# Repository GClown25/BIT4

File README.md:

# BIT4
BIT4 is a 4Bit microcontroller - fully programmable with only three buttons.

# Programming guide:

The BIT4 microcontroller has 256 Bytes of programm memory, split in 16 pages with each 16 instructions.
A instruction is 8bit wide and consists of an command and data:
\

\
To enter the programming mode, hold BTN2 down, press the RESET button once and then release BTN2.
In programming mode, step through the instructions with BTN2. When going to a new instruction, 
the leds will show the current address for a fraktion of a second.
With BTN1 the value of the command and data of the current instruction can be changed.
When stepping to a new address with BTN2, the instuction of the address above gets saved in the EEPROM.
At the end, press RESET to leave the programming mode and to start the programm execution.

## Instruction set explained:

- command 0x0: load a constant value to doutB
- command 0x1: load a constant value to doutA
- command 0x2: delay
- command 0x3: do a relative jump back
- command 0x4: load constant value to variable A
- command 0x5: load something with the value of variable A
- command 0x6: load the value of something into the variable A
- command 0x7: do arithmetic and logic operations with variable A (and B)
- command 0x8: set the high nibble of the address to jump to in absolute jump instructions
- command 0x9: do an absolute jump to the specified address
- command 0xA, 0xB: acts like a for loop. Every time this command is executed,
  if the variable C (or D) is greater than zero, an absolute jump to the specified address is done.
  Then the variable C (or D) gets decremented. 
- command 0xC: skip the next instruction if the argument is true
- command 0xD: call a function at the specified address
- command 0xE: return from the function call
- command 0xF: sets the address of the virtual 4bit RAM. 
  The value stored in this address can be read with 0x6e and written with 0x50.

## Examples:

**Blinki:**

| address | instruction |                    comment |
| :------ | :---------- | -------------------------: |
| 0       | 1f          |  turn all leds on doutA on |
| 1       | 28          |             wait for 500ms |
| 2       | 10          | turn all leds on doutB off |
| 3       | 28          |             wait for 500ms |
| 4       | 34          |           relative jump -4 |

\
**Binary counter:**
\
https://www.youtube.com/watch?v=6CpZszKlP7Y

| address | instruction |          comment |
| :------ | :---------- | ---------------: |
| 0       | 5B          |        DoutB = A |
| 1       | 59          |         PWM1 = A |
| 2       | 71          |              A++ |
| 3       | 28          |   wait for 500ms |
| 4       | 34          | relative jump -4 |

\
**Blinki with adjustable speed:**
\
https://www.youtube.com/watch?v=YPoedGGZs4g

| address   | instruction |               comment |
| :-------- | :---------- | --------------------: |
| **main:** |
| 0         | 10          |           DoutA = 0x0 |
| 1         | d5          |           call myWait |
| 2         | 1f          |           DoutA = 0xf |
| 3         | d5          |           call myWait |
| 4         | 34          |      relative jump -4 |
| **myWait:** |
| 5         | 64          |               A = Din |
| 6         | 52          |                 C = A |
| 7         | 25          |         wait for 50ms |
| 8         | a7          | for(C > 0; C--) jmp 7 |
| 9         | e0          |                return |

\
**Credits:**\
The idea for this project came from the german microcontroller learning plattform "TPS" (http://elektronik-labor.de/Lernpakete/TPS/TPS0.html).

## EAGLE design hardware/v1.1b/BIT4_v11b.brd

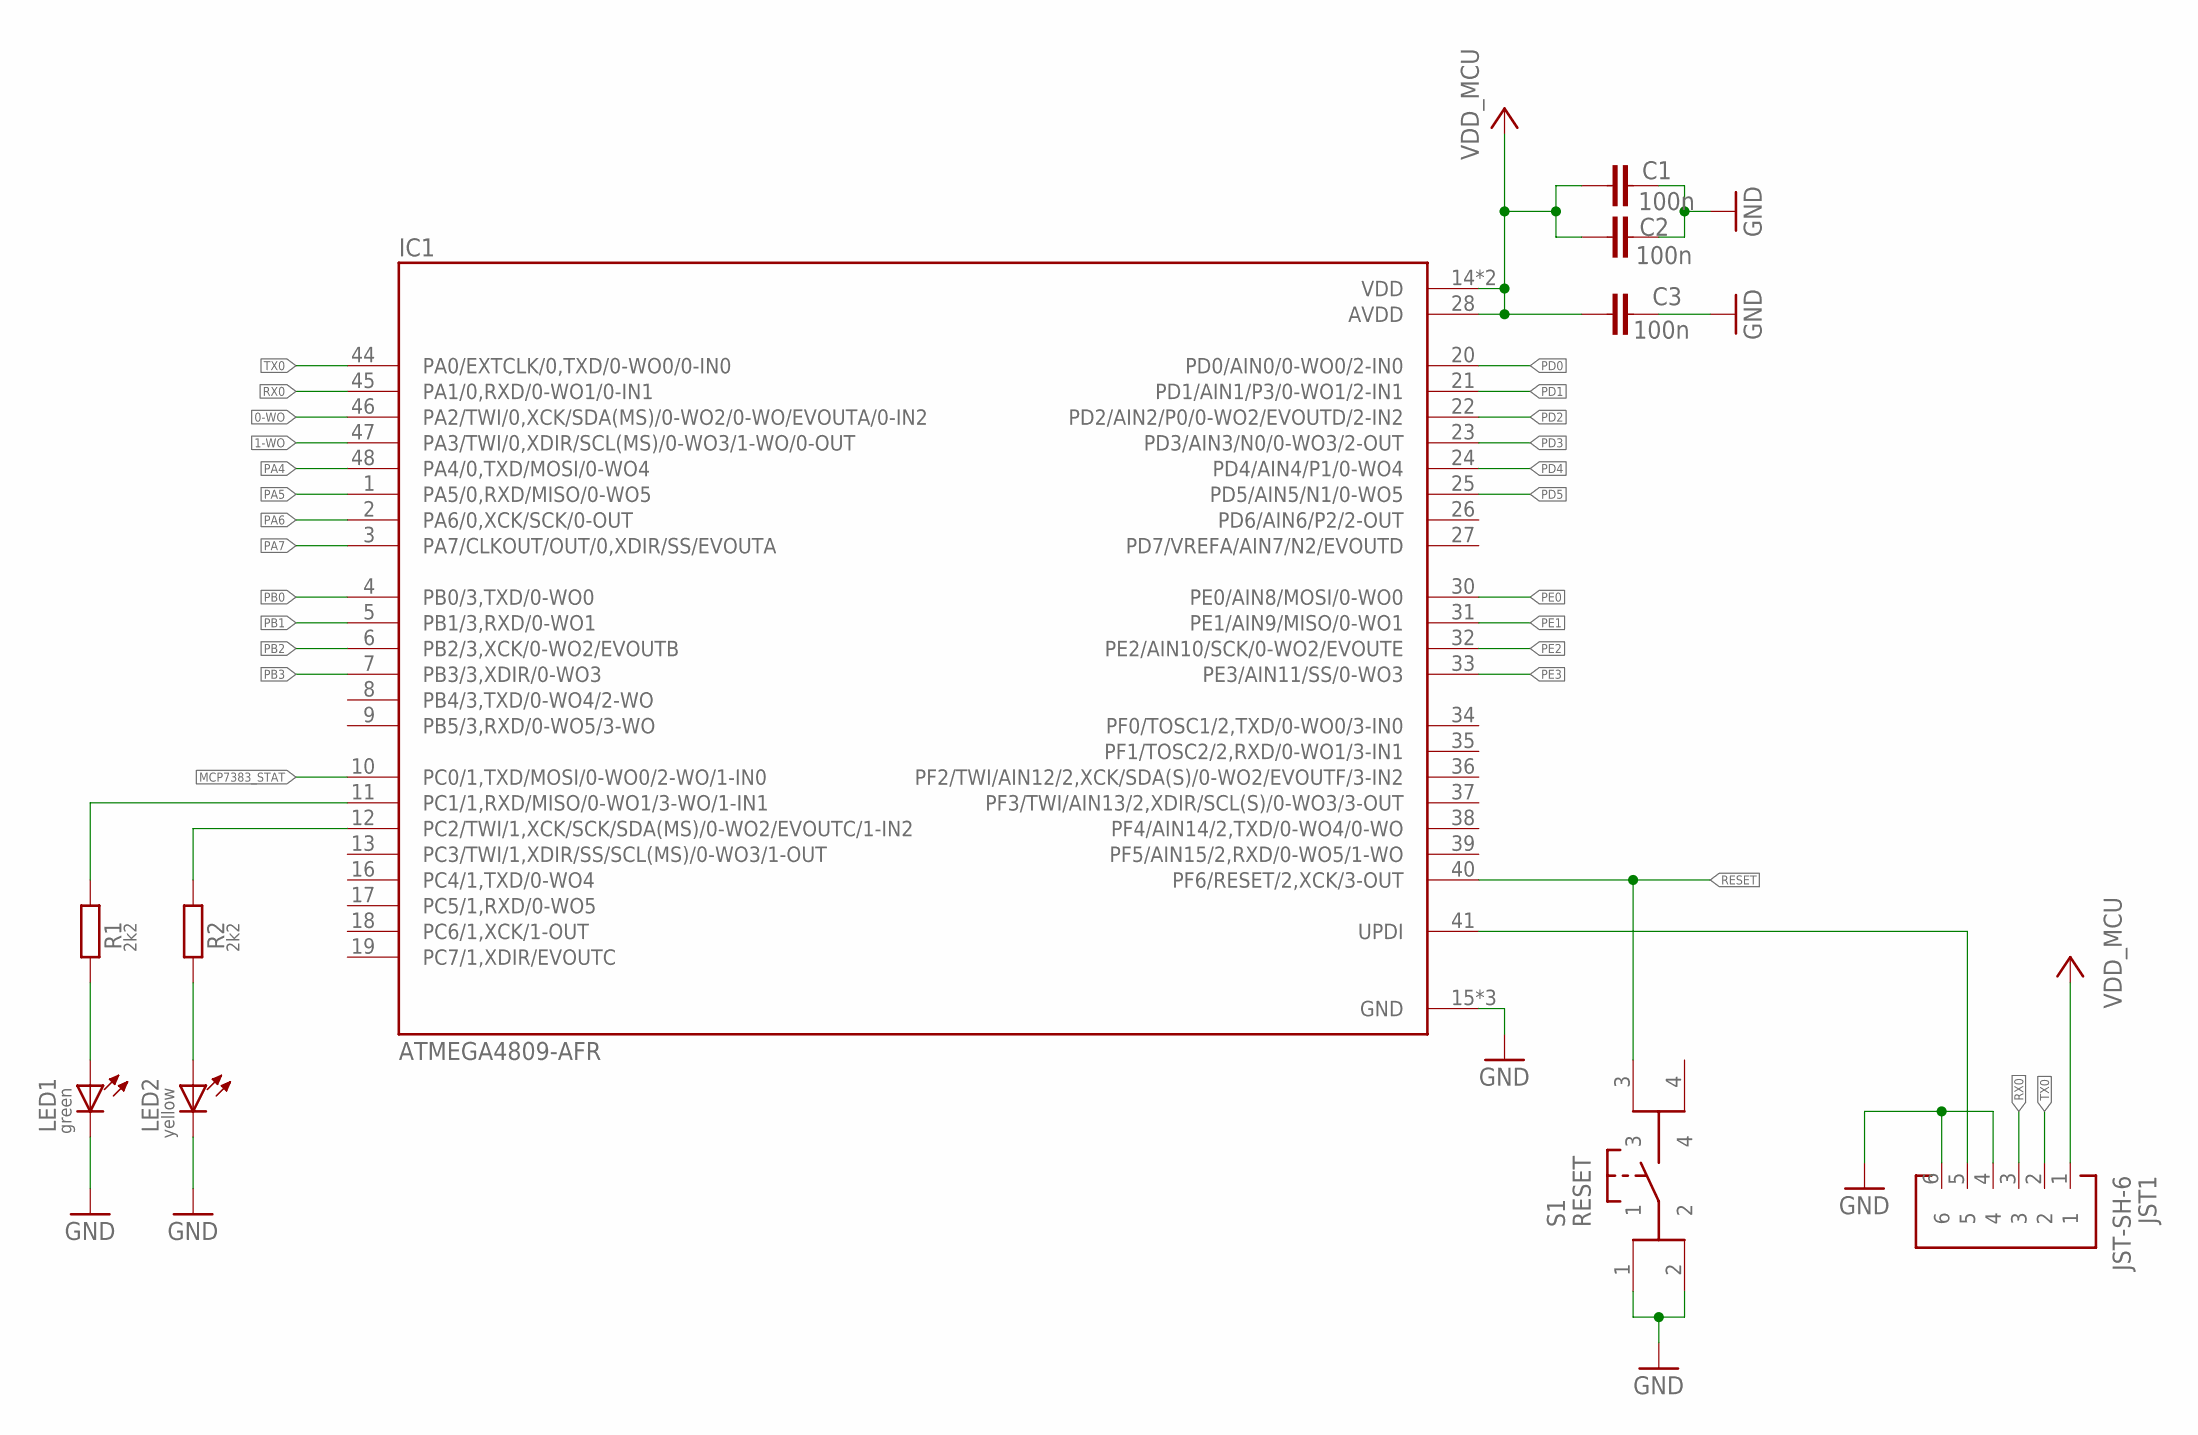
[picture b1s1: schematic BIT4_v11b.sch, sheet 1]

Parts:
C1, C2, C3: 100n; C0603
IC1: ATMEGA4809-AFR; QFP50P900X900X120-48N
JST1: JST-SH-6
LED1: green; LED_0603
LED2: yellow; LED_0603
R1, R2: 2k2; R0603
S1: RESET; B3FS-1012

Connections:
0-WO: IC1.46 (PA2/TWI/0,XCK/SDA(MS)/0-WO2/0-WO/EVOUTA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); also elsewhere on the board
1-WO: IC1.47 (PA3/TWI/0,XDIR/SCL(MS)/0-WO3/1-WO/0-OUT); also elsewhere on the board
GND: C1.2, C2.2, C3.2, IC1.15 (GND), IC1.29 (GND), IC1.43 (GND), JST1.4, JST1.6, LED1.C, LED2.C, S1.1, S1.2; also elsewhere on the board
MCP7383_STAT: IC1.10 (PC0/1,TXD/MOSI/0-WO0/2-WO/1-IN0); also elsewhere on the board
unnamed: LED2.A, R2.1
unnamed: LED1.A, R1.1
unnamed: IC1.12 (PC2/TWI/1,XCK/SCK/SDA(MS)/0-WO2/EVOUTC/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), R2.2
unnamed: IC1.11 (PC1/1,RXD/MISO/0-WO1/3-WO/1-IN1), R1.2
PA4: IC1.48 (PA4/0,TXD/MOSI/0-WO4); also elsewhere on the board
PA5: IC1.1 (PA5/0,RXD/MISO/0-WO5); also elsewhere on the board
PA6: IC1.2 (PA6/0,XCK/SCK/0-OUT); also elsewhere on the board
PA7: IC1.3 (PA7/CLKOUT/OUT/0,XDIR/SS/EVOUTA); also elsewhere on the board
PB0: IC1.4 (PB0/3,TXD/0-WO0); also elsewhere on the board
PB1: IC1.5 (PB1/3,RXD/0-WO1); also elsewhere on the board
PB2: IC1.6 (PB2/3,XCK/0-WO2/EVOUTB); also elsewhere on the board
PB3: IC1.7 (PB3/3,XDIR/0-WO3); also elsewhere on the board
PD0: IC1.20 (PD0/AIN0/0-WO0/2-IN0); also elsewhere on the board
PD1: IC1.21 (PD1/AIN1/P3/0-WO1/2-IN1); also elsewhere on the board
PD2: IC1.22 (PD2/AIN2/P0/0-WO2/EVOUTD/2-IN2); also elsewhere on the board
PD3: IC1.23 (PD3/AIN3/N0/0-WO3/2-OUT); also elsewhere on the board
PD4: IC1.24 (PD4/AIN4/P1/0-WO4); also elsewhere on the board
PD5: IC1.25 (PD5/AIN5/N1/0-WO5); also elsewhere on the board
PE0: IC1.30 (PE0/AIN8/MOSI/0-WO0); also elsewhere on the board
PE1: IC1.31 (PE1/AIN9/MISO/0-WO1); also elsewhere on the board
PE2: IC1.32 (PE2/AIN10/SCK/0-WO2/EVOUTE); also elsewhere on the board
PE3: IC1.33 (PE3/AIN11/SS/0-WO3); also elsewhere on the board
RESET: IC1.40 (PF6/RESET/2,XCK/3-OUT), S1.3
RX0: IC1.45 (PA1/0,RXD/0-WO1/0-IN1), JST1.3
TX0: IC1.44 (PA0/EXTCLK/0,TXD/0-WO0/0-IN0), JST1.2
UPDI: IC1.41 (UPDI), JST1.5
VDD_MCU: C1.1, C2.1, C3.1, IC1.14 (VDD), IC1.28 (AVDD), IC1.42 (VDD), JST1.1; also elsewhere on the board

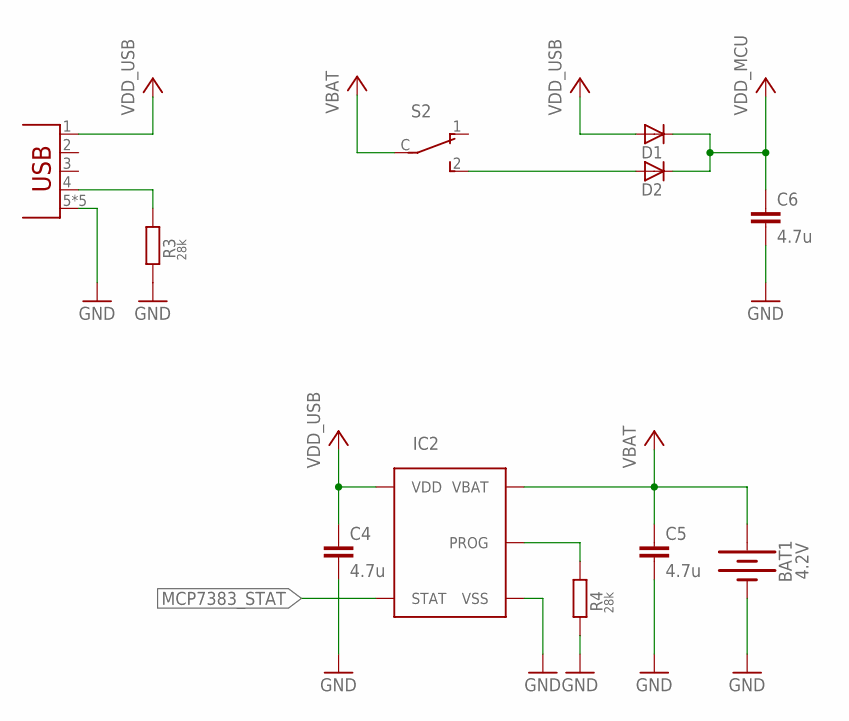
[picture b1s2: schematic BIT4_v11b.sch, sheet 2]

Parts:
BAT1: 4.2V; CELL-CLIP_PAD_20MM
C4, C5, C6: 4.7u; C0603
D1, D2: DIODE; MBR0530T1
IC2: MCP7383; SOT23-5
R3, R4: 28k; R0603
S2: SWITCH; ESP40XX
USB1: USB; 629105136821

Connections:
GND: BAT1.-, C4.2, C5.2, C6.2, IC2.2 (VSS), R3.1, R4.1, USB1.5 (GND), USB1.Z1 (GND), USB1.Z2 (GND), USB1.Z3 (GND), USB1.Z4 (GND); also elsewhere on the board
MCP7383_STAT: IC2.1 (STAT); also elsewhere on the board
unnamed: R3.2, USB1.4 (USBID)
unnamed: D2.P$1 (A), S2.2
unnamed: IC2.5 (PROG), R4.2
VBAT: BAT1.+1 (+), BAT1.+2 (+), C5.1, IC2.3 (VBAT), S2.C
VDD_MCU: C6.1, D1.P$2 (C), D2.P$2 (C); also elsewhere on the board
VDD_USB: C4.1, D1.P$1 (A), IC2.4 (VDD), USB1.1 (VBUS)

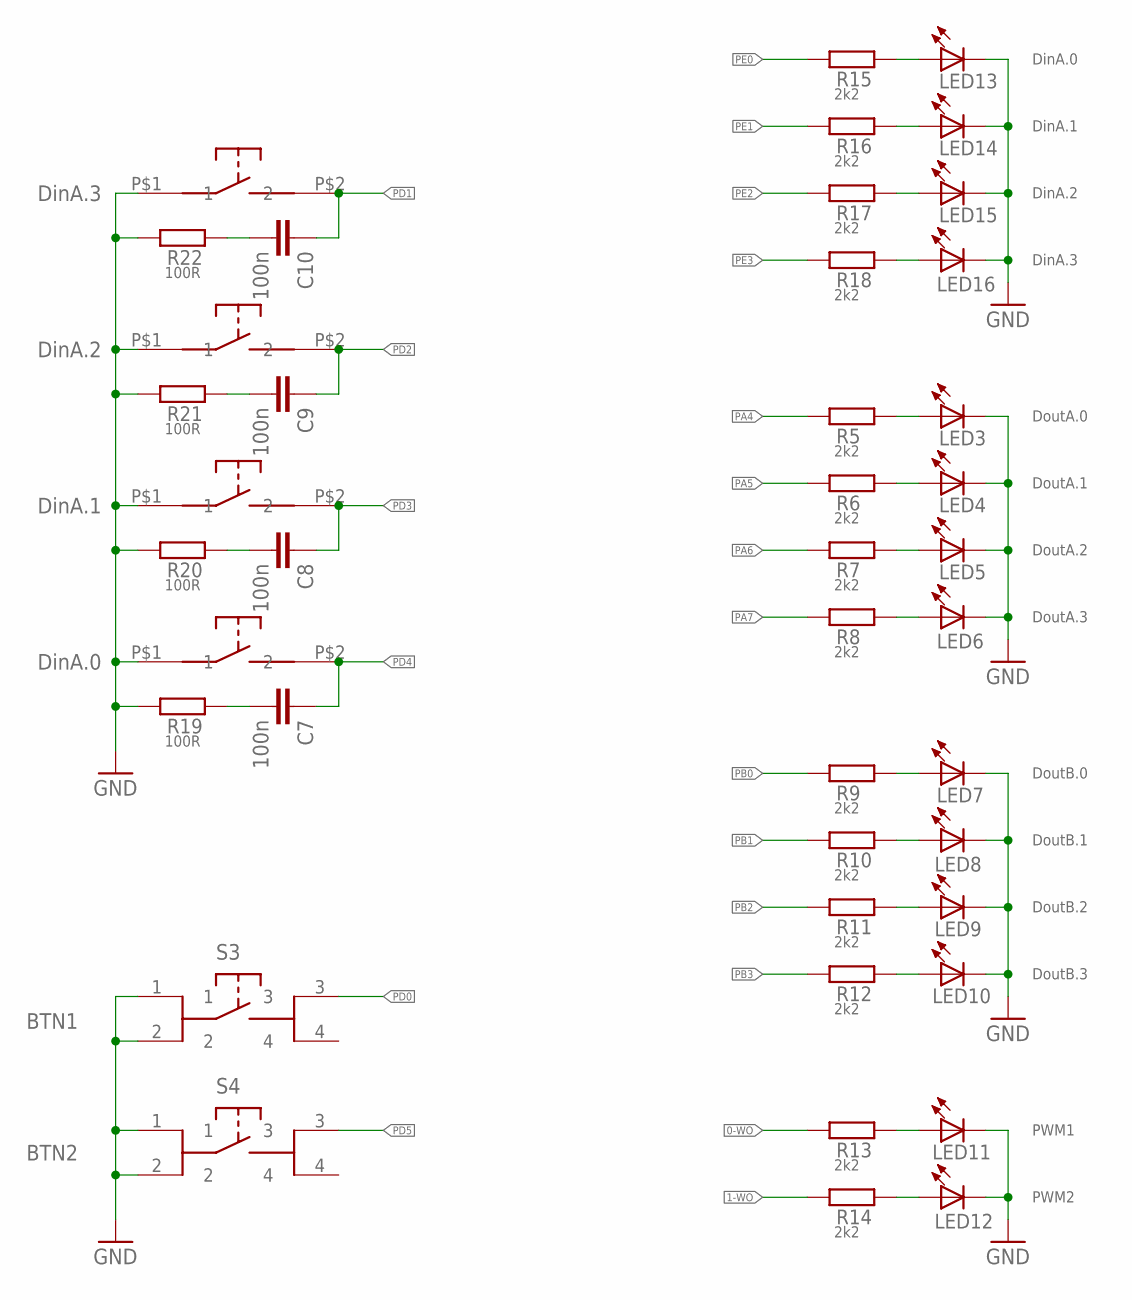
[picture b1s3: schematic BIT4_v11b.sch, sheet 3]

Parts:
C7, C8, C9, C10: 100n; C0603
LED3: DoutA.0; LED_1206
LED4: DoutA.1; LED_1206
LED5: DoutA.2; LED_1206
LED6: DoutA.3; LED_1206
LED7: DoutB.0; LED_1206
LED8: DoutB.1; LED_1206
LED9: DoutB.2; LED_1206
LED10: DoutB.3; LED_1206
LED11: PWM1; LED_1206
LED12: PWM2; LED_1206
LED13: DinA.0; LED_1206
LED14: DinA.1; LED_1206
LED15: DinA.2; LED_1206
LED16: DinA.3; LED_1206
R5, R6, R7, R8, R9, R10, R11, R12, R13, R14, R15, R16, R17, R18: 2k2; R0603
R19, R20, R21, R22: 100R; R0603
S3: BTN1; B3FS-1012
S4: BTN2; B3FS-1012
U$1: DinA.3; BTN_3X6X2.5
U$2: DinA.2; BTN_3X6X2.5
U$3: DinA.1; BTN_3X6X2.5
U$4: DinA.0; BTN_3X6X2.5

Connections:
0-WO: R13.1; also elsewhere on the board
1-WO: R14.1; also elsewhere on the board
GND: LED3.C, LED4.C, LED5.C, LED6.C, LED7.C, LED8.C, LED9.C, LED10.C, LED11.C, LED12.C, LED13.C, LED14.C, LED15.C, LED16.C, R19.1, R20.1, R21.1, R22.1, S3.1, S3.2, S4.1, S4.2, U$1.P$1 (1), U$2.P$1 (1), U$3.P$1 (1), U$4.P$1 (1); also elsewhere on the board
unnamed: LED13.A, R15.2
unnamed: LED14.A, R16.2
unnamed: LED15.A, R17.2
unnamed: LED16.A, R18.2
unnamed: C10.2, R22.2
unnamed: C9.2, R21.2
unnamed: C8.2, R20.2
unnamed: C7.2, R19.2
unnamed: LED3.A, R5.2
unnamed: LED4.A, R6.2
unnamed: LED5.A, R7.2
unnamed: LED6.A, R8.2
unnamed: LED7.A, R9.2
unnamed: LED8.A, R10.2
unnamed: LED9.A, R11.2
unnamed: LED10.A, R12.2
unnamed: LED11.A, R13.2
unnamed: LED12.A, R14.2
PA4: R5.1; also elsewhere on the board
PA5: R6.1; also elsewhere on the board
PA6: R7.1; also elsewhere on the board
PA7: R8.1; also elsewhere on the board
PB0: R9.1; also elsewhere on the board
PB1: R10.1; also elsewhere on the board
PB2: R11.1; also elsewhere on the board
PB3: R12.1; also elsewhere on the board
PD0: S3.3; also elsewhere on the board
PD1: C10.1, U$1.P$2 (2); also elsewhere on the board
PD2: C9.1, U$2.P$2 (2); also elsewhere on the board
PD3: C8.1, U$3.P$2 (2); also elsewhere on the board
PD4: C7.1, U$4.P$2 (2); also elsewhere on the board
PD5: S4.3; also elsewhere on the board
PE0: R15.1; also elsewhere on the board
PE1: R16.1; also elsewhere on the board
PE2: R17.1; also elsewhere on the board
PE3: R18.1; also elsewhere on the board

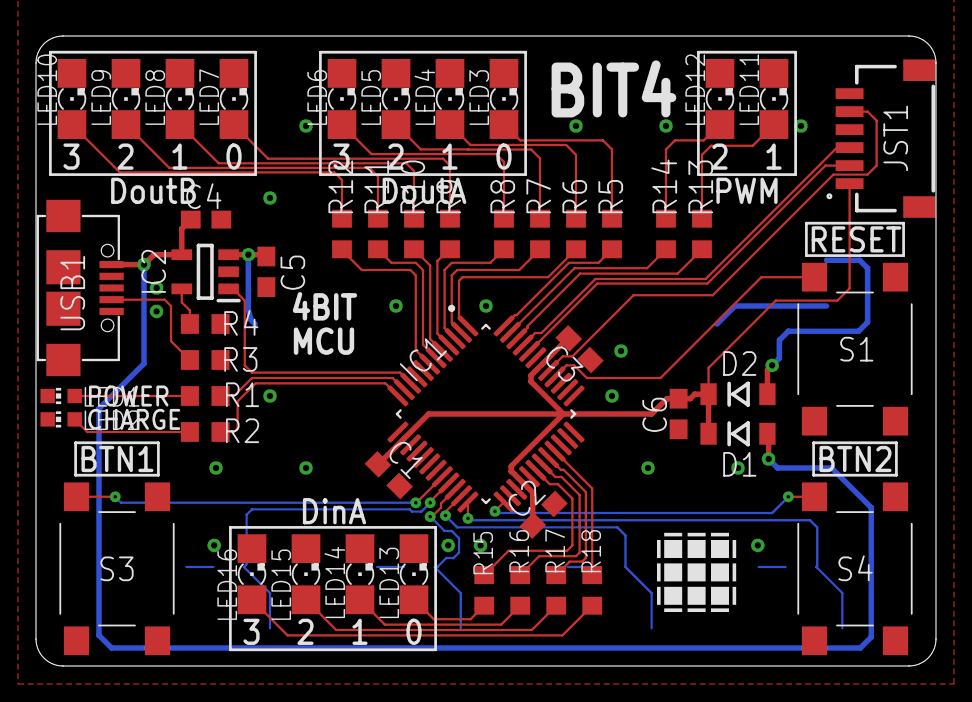
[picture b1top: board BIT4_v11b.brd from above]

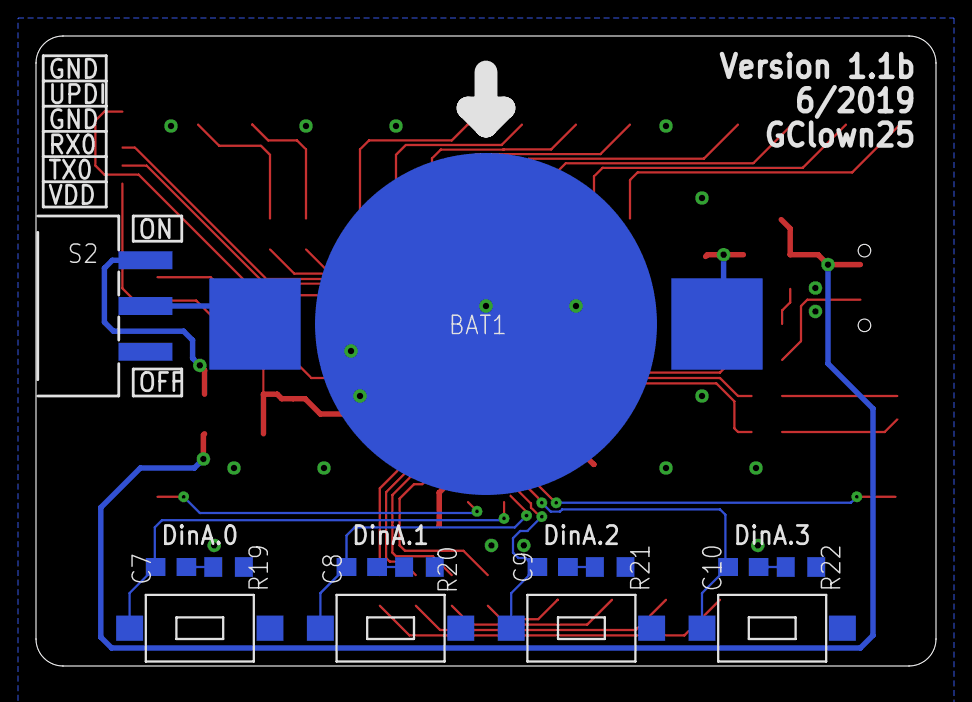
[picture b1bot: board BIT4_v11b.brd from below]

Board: 2 copper layers, 50.0 x 35.0 mm, 63 parts (14 on the bottom side), 54 nets.

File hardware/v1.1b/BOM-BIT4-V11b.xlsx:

pieces | identifier | name | package | prize/piece | prize | link
1 | IC1 | Atmega4809 | TQFP 48-Pin | 1.34 | 1.34 | https://www.mouser.at/ProductDetail/556-ATMEGA4809-AFR
1 | IC2 | MCP7383 Li-ion charger | SOT23-5 | 0.41 | 0.41 | https://www.reichelt.at/battery-management-ic-li-ion-sot-23-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
1 | USB1 | micro usb type B | smd | 0.78 | 0.78 | https://www.mouser.at/ProductDetail/538-47346-0001
1 | JST1 | JST-SH-6 connector | smd 90° | 0.56000000000000005 | 0.56000000000000005 | https://at.rs-online.com/web/p/leiterplatten-header/5468827/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
1 | BAT1 | cell battery clip 20mm | smd | 0.25 | 0.25 | https://www.mouser.at/ProductDetail/712-BAT-HLD-001
2 | D1, D2 | MBR0530T1G schottky diode | SOD-123 | 7.0000000000000007E-2 | 0.14000000000000001 | https://www.reichelt.at/schottkydiode-30-v-0-5-a-sod-123-mbr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
3 | S1, S3, S4 | button 6x6x4.3 mm | smd | 0.28000000000000003 | 0.84000000000000008 | https://www.reichelt.at/taster-smd-1-schliesser-no-omr-b3fs-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
4 | U$1-U$4 | button 3x6x2.5mm | smd | 0.03 | 0.12 | https://www.banggood.com/100pcs-3-x-6-x-2_5mm-DC-12V-0_5A-SM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
1 | S2 | switch 10x6.5x2.5 mm | smd | 1 | 1 | https://www.reichelt.at/schiebeschalter-1x-um-liegend-smd-ss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
1 | LED1 | led green | 0603 | 7.0000000000000007E-2 | 7.0000000000000007E-2 | https://www.reichelt.at/led-smd-0603-gruen-16-mcd-100-evl-19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
1 | LED2 | led yellow | 0603 | 7.0000000000000007E-2 | 7.0000000000000007E-2 | https://www.reichelt.at/led-smd-0603-gelb-16-mcd-100-evl-19-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
4 | LED3-LED6 | led DoutA | 1206 | 0.08 | 0.32 | https://www.reichelt.at/led-smd-1206-rot-62-mcd-60-evl-11-21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
4 | LED7-LED10 | led DoutB | 1206 | 0.08 | 0.32 | https://www.reichelt.at/led-smd-1206-rot-62-mcd-60-evl-11-21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
4 | LED13-LED16 | led DinA | 1206 | 0.09 | 0.36 | https://www.reichelt.at/led-smd-1206-gruen-44-mcd-60-evl-11-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
2 | LED11, LED12 | led PWM | 1206 | 0.36 | 0.72 | https://www.reichelt.at/led-smd-1206-blau-44-mcd-20-evl-11-2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
2 | R3, R4 | resistor 28k | 0603 | 0.02 | 0.04 | https://www.reichelt.at/smd-widerstand-0603-28-0-kohm-100-mw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
16 | R1, R2, R5-R18 | resistor 2k2 | 0603 | 0.02 | 0.32 | https://www.reichelt.at/smd-widerstand-0603-2-2-kohm-100-mw-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
4 | R19-R22 | resistor 100R | 0603 | 0.02 | 0.08 | https://www.reichelt.at/smd-widerstand-0603-100-ohm-100-mw-1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
3 | C4-C6 | capacitor 4u7 | 0603 | 7.0000000000000007E-2 | 0.21000000000000002 | https://www.reichelt.at/vielschicht-kerko-4-7-f-10v-85-c-kem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
7 | C1-C3, C7-C10 | capacitor 100n | 0603 | 0.02 | 0.14000000000000001 | https://www.reichelt.at/smd-vielschicht-keramikkondensator-1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
 |  |  |  |  | 8.0900000000000016

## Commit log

2019-04-11 Added LICENSE
2019-04-11 Added hardware v1.0
2019-04-13 Added source files
2019-04-13 Added AtmelStudio project
2019-04-13 Updated README with a pinout
2019-04-13 Added istruction set
2019-04-14 Added documentation
    ~moved instruction set in the documentation folder
    +added img folder with image of an instruction
    +added programming guide
    +added getting started (not finished)
2019-04-15 Update programming guide
2019-04-15 Updated documentation
2019-04-20 Update README.md with youtube links
2019-04-20 Update README.md with credits
2019-04-24 Updated firmware
    -5C-5F (DoutB bitwise read)
    -6B (A = randNr. [experimental])
    -6C-6D (read Dout ports)
2019-04-27 Updated hardware
    -changed clearance for default netclass to 5mil
2019-07-07 Refactored main.c
2019-07-07 Added debug pin support
2019-08-09 Added firmware support for v1.1b
2019-08-09 Added v1.1b hardware
2019-09-15 Added dynamic RAM access (Write)
2020-05-01 added image of the 'thing'
